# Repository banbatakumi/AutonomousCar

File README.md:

# AutonomousCar

自律走行ミニカー **SURGE Mark.2** の STM32 ファームウェアと基板（回路）。

**技術解説サイト: https://banbatakumi.github.io/surge-mk2/**
ファームの制御（車速制御・TC・ABS・トルクベクタリング・安全層）と基板もこのサイトで解説しています。

> **ファームウェアの最新は [`FW/MainBoard_V3`](https://github.com/banbatakumi/AutonomousCar/tree/FW/MainBoard_V3) ブランチです。**
> 既定ブランチ `main` の `Program/` は古い状態のままです。

## 構成

| ディレクトリ | 内容 |
|---|---|
| `Program/MainF446RE_V3/` | 現行ファーム（STM32F446RE）。最新は上記ブランチ。`Program/MainF446RE`・`MainF446RE_V2` は旧版 |
| `Circuit/` | 基板の設計（`MainBoard_V1`〜`V3_2`、`OtherBoard_V1`） |

## 関連リポジトリ

[`AutonomousCar_RasPi`](https://github.com/banbatakumi/AutonomousCar_RasPi) — Raspberry Pi 側のプログラム。
Pi とは UART（1 Mbps）で通信します。プロトコル（`RAS_PROTOCOL_VERSION`）は Pi 側と**セットで**入れ替えます。

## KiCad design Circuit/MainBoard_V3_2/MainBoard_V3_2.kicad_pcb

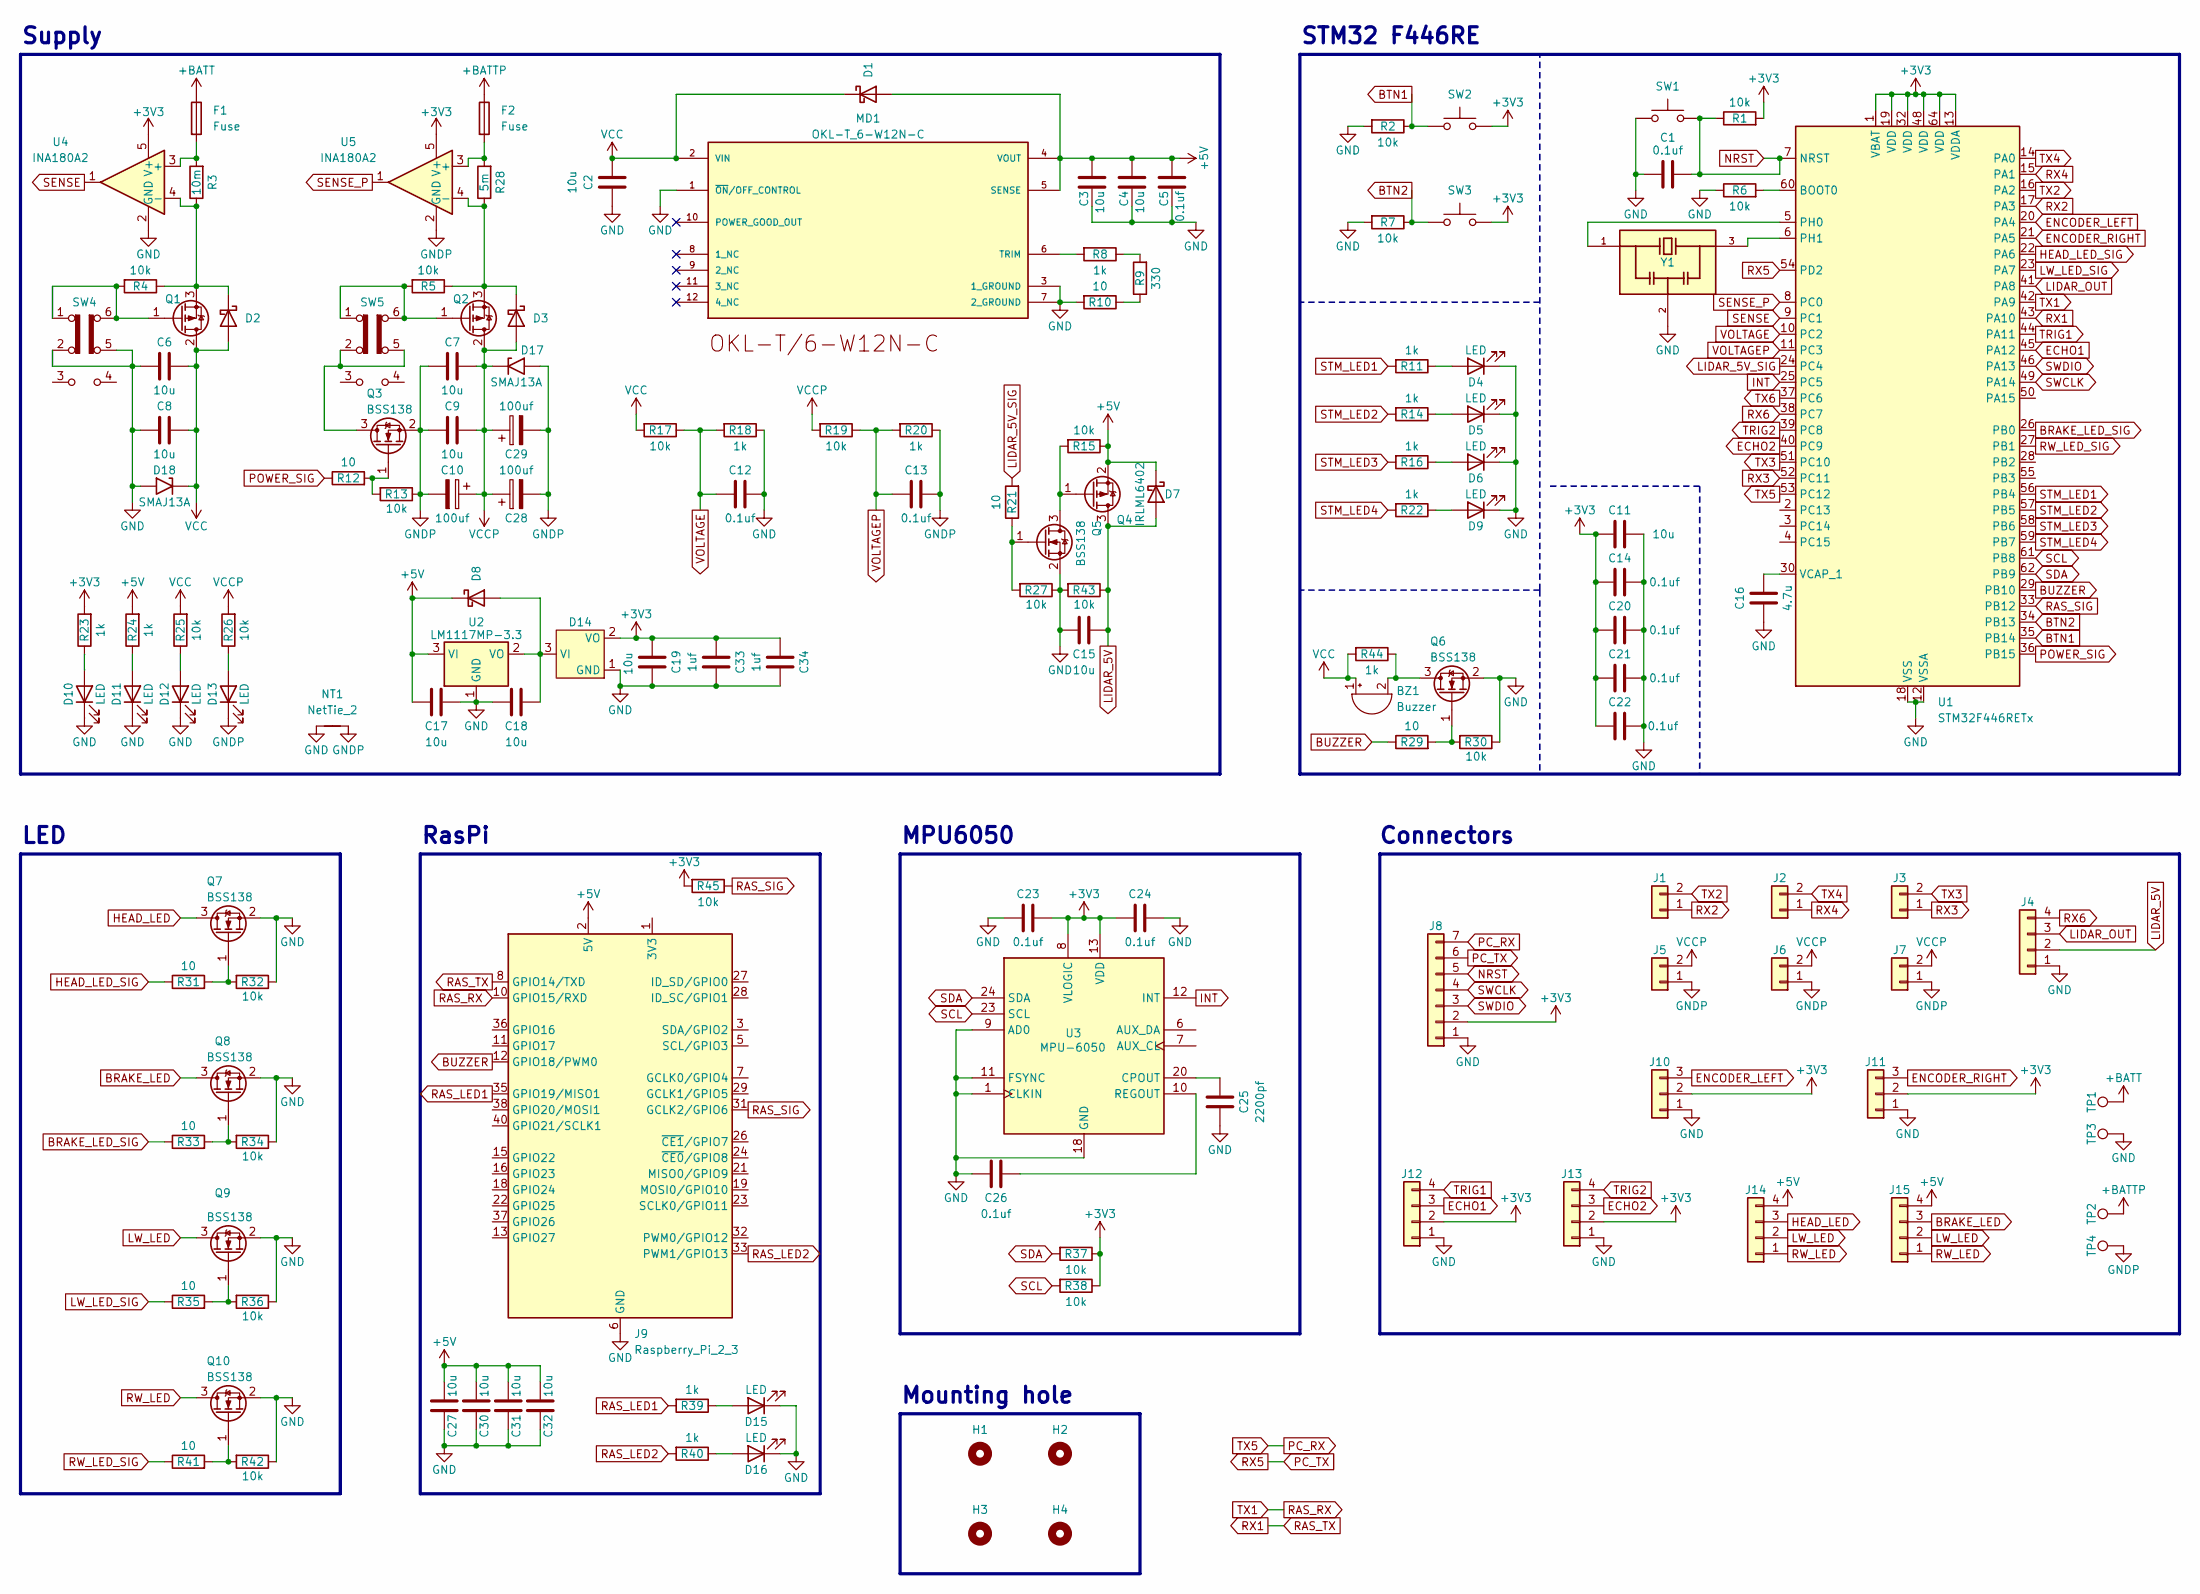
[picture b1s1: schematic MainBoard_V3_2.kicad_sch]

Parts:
BZ1: Buzzer; Buzzer_Murata_PKLCS1212E
C1, C5, C12, C13, C14, C20, C21, C22, C23, C24, C26: 0.1uf; C_0603_1608Metric
C2, C3, C4, C6, C7, C8, C9, C11, C15, C17, C18, C19, C27, C30, C31, C32: 10u; C_0805_2012Metric
C10, C28, C29: 100uf; CP_Radial_D6.3mm_P2.50mm
C16: 4.7u; C_0805_2012Metric
C25: 2200pf; C_0603_1608Metric
C33, C34: 1uf; C_0603_1608Metric
D1, D2, D3, D7, D8: D_Schottky; D_SOD-323_HandSoldering
D4, D5, D6, D9, D10, D11, D12, D13, D15, D16: LED; LED_0603_1608Metric
D14: CH213K; TSOT-23
D17, D18: SMAJ13A; D_SMA
F1, F2: Fuse; Fuseholder_Clip-5x20mm_Keystone_3517_Inline_P23.11x6.76mm_D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
H1, H2, H3, H4: MountingHole; MountingHole_3.2mm_M3_Pad_Via
J1, J2, J3: Conn_01x02; JST_PH_S2B-PH-K_1x02_P2.00mm_Horizontal
J4, J12, J13: Conn_01x04; JST_XH_S4B-XH-A_1x04_P2.50mm_Horizontal
J5, J6, J7: Conn_01x02; Molex_SPOX_5268-02A_1x02_P2.50mm_Horizontal
J8: Conn_01x07; JST_PH_S7B-PH-K_1x07_P2.00mm_Horizontal
J9: Raspberry_Pi_2_3; raspberreyPi
J10, J11: Conn_01x03; JST_PH_S3B-PH-K_1x03_P2.00mm_Horizontal
J14, J15: Conn_01x04; JST_PH_S4B-PH-K_1x04_P2.00mm_Horizontal
MD1: OKL-T_6-W12N-C; MURATA_OKL-T-6-W12N-C_0; MOUSER_PART_NUMBER 580-OKL-T/6-W12N-C; MOUSER_DESCRIPTION Non-Isolated DC/DC Converters 12Vin .59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
NT1: NetTie_2; NetTie-2_SMD_Pad0.5mm
Q1, Q2: Q_PMOS_GDS; TO-252-2
Q3, Q5, Q6, Q7, Q8, Q9, Q10: BSS138; SOT-23
Q4: IRLML6402; SOT-23
R1, R2, R4, R5, R6, R7, R13, R15, R17, R19, R25, R26, R27, R30, R32, R34, R36, R37, R38, R42, R43, R45: 10k; R_0603_1608Metric
R3: 10m; R_1206_3216Metric
R8, R11, R14, R16, R18, R20, R22, R23, R24, R39, R40, R44: 1k; R_0603_1608Metric
R9: 330; R_0603_1608Metric
R10, R12, R21, R29, R31, R33, R35, R41: 10; R_0603_1608Metric
R28: 5m; R_1206_3216Metric
SW1, SW2, SW3: SW_Push; SW_SPST_PTS810
SW4, SW5: SW_Slide_DPDT; IS-2235
TP1, TP2, TP3, TP4: TestPoint; TestPoint_THTPad_D4.0mm_Drill2.0mm
U1: STM32F446RETx; LQFP-64_10x10mm_P0.5mm
U2: LM1117MP-3.3; SOT-223-3_TabPin2
U3: MPU-6050; QFN-24-1EP_4x4mm_P0.5mm_EP2.15x2.15mm
U4, U5: INA180A2; SOT-23-5
Y1: CSTNE16M0V530000R0; Resonator_SMD_Murata_CSTxExxV-3Pin_3.0x1.1mm; PARTREV JGC42-8853B

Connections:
+3V3: C11.1, C14.2, C19.2, C20.2, C21.2, C22.2, C23.1, C24.2, C33.2, C34.2, D14.2 (VO), J8.2, J10.2, J11.2, J12.2, J13.2, R1.2, R23.2, R37.1, R38.1, R45.2, SW2.2, SW3.2, U1.1 (VBAT), U1.13 (VDDA), U1.19 (VDD), U1.32 (VDD), U1.48 (VDD), U1.64 (VDD), U3.8 (VLOGIC), U3.13 (VDD), U4.5 (V+), U5.5 (V+); also elsewhere on the board
+5V: C3.1, C4.1, C5.1, C17.2, C27.1, C30.1, C31.1, C32.1, D1.2 (A), D7.1 (K), D8.1 (K), J9.2 (5V), J9.4 (5V), J14.4, J15.4, MD1.4 (VOUT), MD1.5 (SENSE), Q4.2 (S), R15.1, R24.2, U2.3 (VI); also elsewhere on the board
+BATT: F1.1, TP1.1
+BATTP: F2.1, TP2.1
BRAKE_LED: J15.3, Q8.3 (D)
BRAKE_LED_SIG: R33.1, U1.26 (PB0)
BTN1: R2.1, SW2.1, U1.35 (PB14)
BTN2: R7.1, SW3.1, U1.34 (PB13)
BUZZER: J9.12 (GPIO18/PWM0), R29.1, U1.29 (PB10)
ECHO1: J12.3, U1.45 (PA12)
ECHO2: J13.3, U1.40 (PC9)
ENCODER_LEFT: J10.3, U1.20 (PA4)
ENCODER_RIGHT: J11.3, U1.21 (PA5)
GND: C1.1, C2.1, C3.2, C4.2, C5.2, C6.2, C8.2, C11.2, C12.1, C14.1, C15.2, C16.2, C17.1, C18.2, C19.1, C20.1, C21.1, C22.1, C23.2, C24.1, C25.2, C26.2, C27.2, C30.2, C31.2, C32.2, C33.1, C34.1, D4.1 (K), D5.1 (K), D6.1 (K), D9.1 (K), D10.1 (K), D11.1 (K), D12.1 (K), D14.1 (GND), D15.1 (K), D16.1 (K), D18.2 (A2), J4.1, J8.1, J9.6 (GND), J9.9 (GND), J9.14 (GND), J9.20 (GND), J9.25 (GND), J9.30 (GND), J9.34 (GND), J9.39 (GND), J10.1, J11.1, J12.1, J13.1, MD1.1 (~ON/OFF_CONTROL), MD1.3 (1_GROUND), MD1.7 (2_GROUND), NT1.1, Q5.2 (S), Q6.2 (S), Q7.2 (S), Q8.2 (S), Q9.2 (S), Q10.2 (S), R2.2, R6.1, R7.2, R10.2, R18.1, R27.1, R30.1, R32.1, R34.1, R36.1, R42.1, R43.2, SW1.1, SW4.2 (B), SW4.5 (B), TP3.1, U1.12 (VSSA), U1.18 (VSS), U1.31 (VSS), U1.47 (VSS), U1.63 (VSS), U2.1 (GND), U3.1 (CLKIN), U3.9 (AD0), U3.11 (FSYNC), U3.18 (GND), U4.2 (GND), Y1.2; also elsewhere on the board
GNDP: C7.1, C9.1, C10.2, C13.1, C28.2, C29.2, D13.1 (K), D17.2 (A2), J5.1, J6.1, J7.1, NT1.2, Q3.2 (S), R13.1, R20.1, TP4.1, U5.2 (GND)
HEAD_LED: J14.3, Q7.3 (D)
HEAD_LED_SIG: R31.1, U1.22 (PA6)
INT: U1.25 (PC5), U3.12 (INT)
LIDAR_5V: C15.1, D7.2 (A), J4.2, Q4.3 (D), R43.1
LIDAR_5V_SIG: R21.2, U1.24 (PC4)
LIDAR_OUT: J4.3, U1.41 (PA8)
LW_LED: J14.2, J15.2, Q9.3 (D)
LW_LED_SIG: R35.1, U1.23 (PA7)
NRST: C1.2, J8.5, R1.1, SW1.2, U1.7 (NRST)
unnamed: BZ1.2 (-), Q6.3 (D), R44.1
unnamed: D2.1 (K), Q1.3 (S), R3.1, R4.1, U4.4 (-)
unnamed: D3.1 (K), Q2.3 (S), R5.1, R28.1, U5.4 (-)
unnamed: D4.2 (A), R11.1
unnamed: D5.2 (A), R14.1
unnamed: D6.2 (A), R16.1
unnamed: D9.2 (A), R22.1
unnamed: D10.2 (A), R23.1
unnamed: D11.2 (A), R24.1
unnamed: D12.2 (A), R25.1
unnamed: D13.2 (A), R26.1
unnamed: C18.1, D8.2 (A), D14.3 (VI), U2.2 (VO)
unnamed: D15.2 (A), R39.1
unnamed: D16.2 (A), R40.1
unnamed: J9.1 (3V3), J9.17 (3V3)
unnamed: MD1.6 (TRIM), R8.2
unnamed: Q1.1 (G), R4.2, SW4.1 (A), SW4.6 (C)
unnamed: Q2.1 (G), R5.2, SW5.1 (A), SW5.6 (C)
unnamed: Q3.3 (D), SW5.2 (B), SW5.5 (B)
unnamed: Q3.1 (G), R12.2, R13.2
unnamed: Q4.1 (G), Q5.3 (D), R15.2
unnamed: Q5.1 (G), R21.1, R27.2
unnamed: Q6.1 (G), R29.2, R30.2
unnamed: Q7.1 (G), R31.2, R32.2
unnamed: Q8.1 (G), R33.2, R34.2
unnamed: Q9.1 (G), R35.2, R36.2
unnamed: Q10.1 (G), R41.2, R42.2
unnamed: R8.1, R9.2
unnamed: R9.1, R10.1
unnamed: R6.2, U1.60 (BOOT0)
unnamed: U1.5 (PH0), Y1.1
unnamed: U1.6 (PH1), Y1.3
unnamed: C16.1, U1.30 (VCAP_1)
unnamed: C25.1, U3.20 (CPOUT)
unnamed: C26.1, U3.10 (REGOUT)
unnamed: F1.2, R3.2, U4.3 (+)
unnamed: F2.2, R28.2, U5.3 (+)
PC_RX: J8.7, U1.53 (PC12)
PC_TX: J8.6, U1.54 (PD2)
POWER_SIG: R12.1, U1.36 (PB15)
RAS_LED1: J9.35 (GPIO19/MISO1), R39.2
RAS_LED2: J9.33 (PWM1/GPIO13), R40.2
RAS_RX: J9.10 (GPIO15/RXD), U1.42 (PA9)
RAS_SIG: J9.31 (GCLK2/GPIO6), R45.1, U1.33 (PB12)
RAS_TX: J9.8 (GPIO14/TXD), U1.43 (PA10)
RW_LED: J14.1, J15.1, Q10.3 (D)
RW_LED_SIG: R41.1, U1.27 (PB1)
RX2: J1.1, U1.17 (PA3)
RX3: J3.1, U1.52 (PC11)
RX4: J2.1, U1.15 (PA1)
RX6: J4.4, U1.38 (PC7)
SCL: R38.2, U1.61 (PB8), U3.23 (SCL)
SDA: R37.2, U1.62 (PB9), U3.24 (SDA)
SENSE: U1.9 (PC1), U4.1
SENSE_P: U1.8 (PC0), U5.1
STM_LED1: R11.2, U1.56 (PB4)
STM_LED2: R14.2, U1.57 (PB5)
STM_LED3: R16.2, U1.58 (PB6)
STM_LED4: R22.2, U1.59 (PB7)
SWCLK: J8.4, U1.49 (PA14)
SWDIO: J8.3, U1.46 (PA13)
TRIG1: J12.4, U1.44 (PA11)
TRIG2: J13.4, U1.39 (PC8)
TX2: J1.2, U1.16 (PA2)
TX3: J3.2, U1.51 (PC10)
TX4: J2.2, U1.14 (PA0)
TX6: U1.37 (PC6)
VCC: BZ1.1 (+), C2.2, C6.1, C8.1, D1.1 (K), D2.2 (A), D18.1 (A1), MD1.2 (VIN), Q1.2 (D), R17.2, R25.2, R44.2
VCCP: C7.2, C9.2, C10.1, C28.1, C29.1, D3.2 (A), D17.1 (A1), J5.2, J6.2, J7.2, Q2.2 (D), R19.2, R26.2
VOLTAGE: C12.2, R17.1, R18.2, U1.10 (PC2)
VOLTAGEP: C13.2, R19.1, R20.2, U1.11 (PC3)

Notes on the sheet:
Mounting hole
LED
Supply
MPU6050
RasPi
Connectors
STM32 F446RE

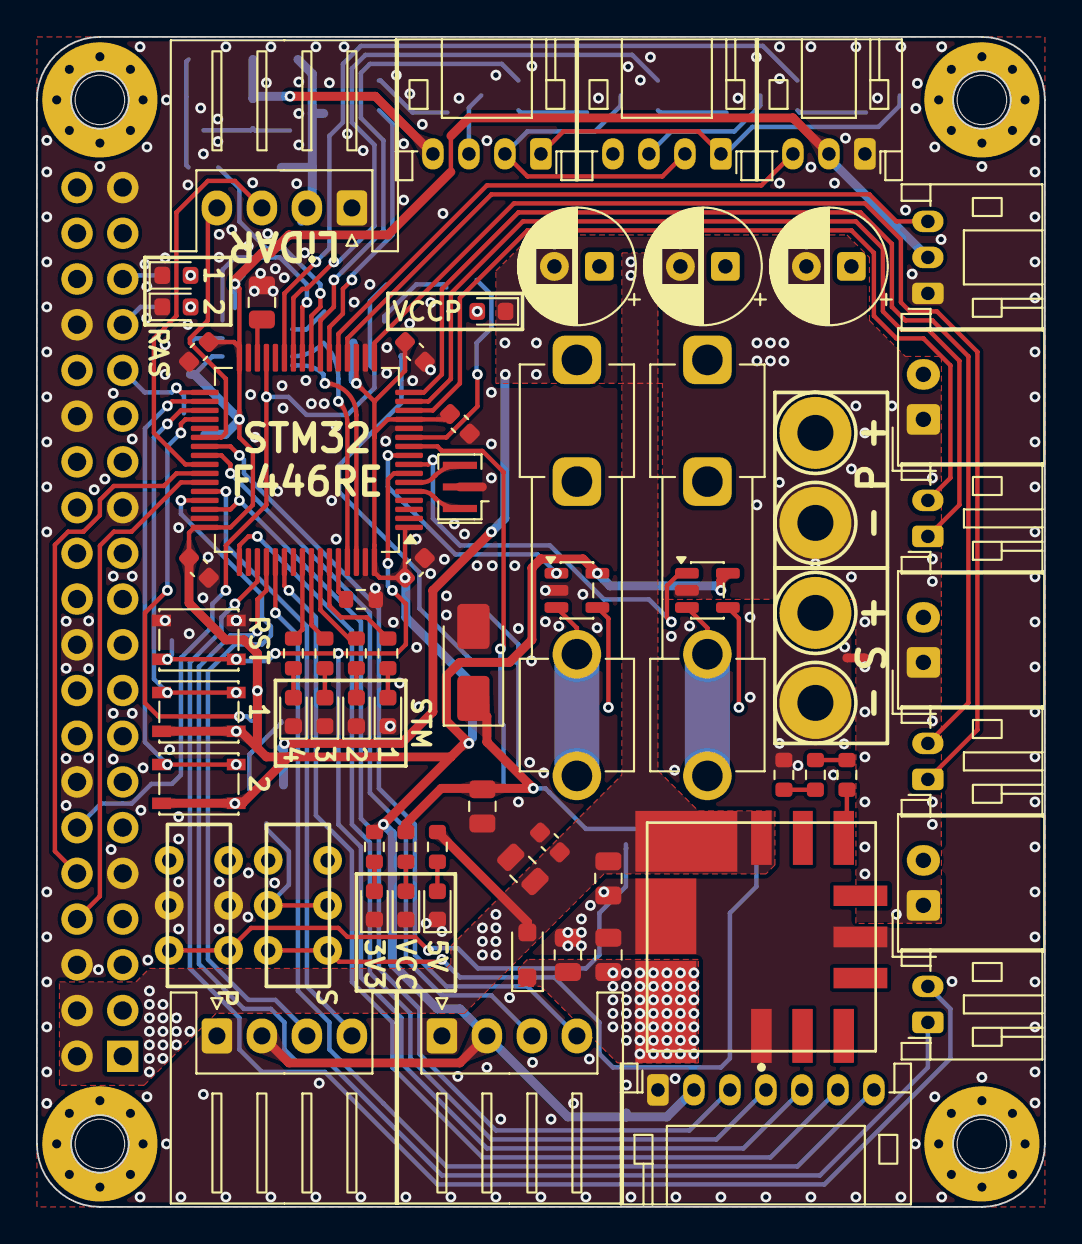
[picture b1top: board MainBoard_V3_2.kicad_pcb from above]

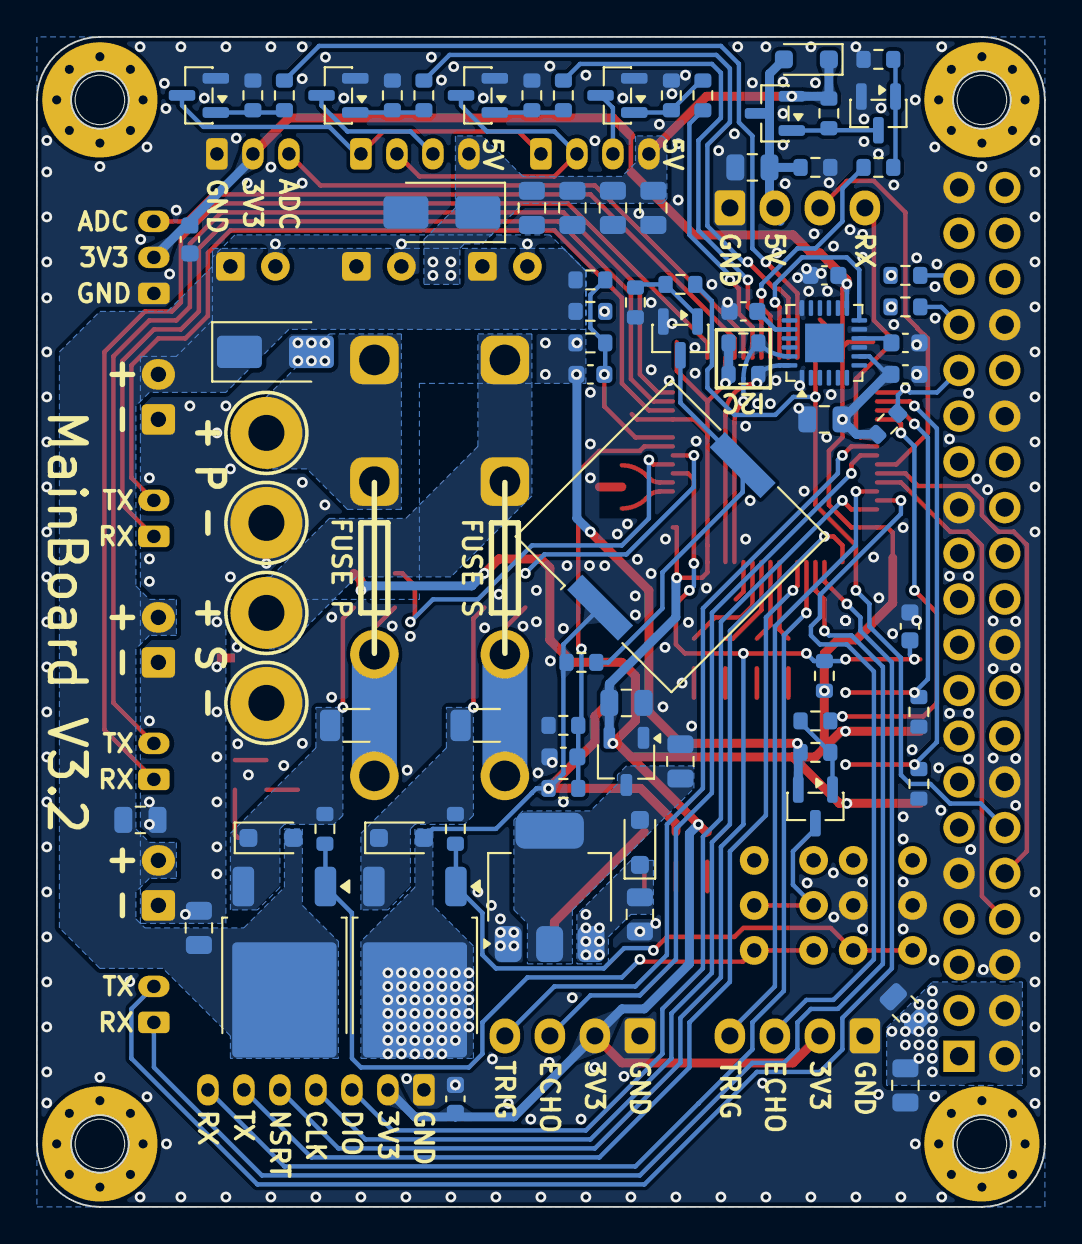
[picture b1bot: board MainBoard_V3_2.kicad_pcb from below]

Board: 2 copper layers, 56.0 x 65.0 mm, 150 parts (80 on the bottom side), 94 nets.

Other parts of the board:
C35: 0.1uf; C_0603_1608Metric
C36, C37: 10u; C_0805_2012Metric
D19: SMAJ5.0A; D_SMA

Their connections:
+3V3: C35.2; also elsewhere on the board
+5V: C36.1, C37.1, D19.1 (A1); also elsewhere on the board
GND: C35.1, C36.2, C37.2, D19.2 (A2); also elsewhere on the board

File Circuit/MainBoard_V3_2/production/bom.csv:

Designator,Footprint,Quantity,Value,LCSC Part #
BZ1,Buzzer_Murata_PKLCS1212E,1,Buzzer,
"C1, C12, C13, C14, C20, C21, C22, C23, C24, C26, C5",0603,11,0.1uf,
"C10, C28, C29",CP_Radial_D6.3mm_P2.50mm,3,100uf,
"C11, C15, C17, C18, C19, C2, C27, C3, C30, C31, C32, C4, C6, C7, C8, C9",0805,16,10u,
C16,0805,1,4.7u,
C25,0603,1,2200pf,
"C33, C34",0603,2,1uf,
"D1, D2, D3, D7, D8",D_SOD-323_HandSoldering,5,D_Schottky,
"D10, D11, D12, D13, D15, D16, D4, D5, D6, D9",0603,10,LED,
D14,TSOT-23,1,CH213K,
"D17, D18",D_SMA,2,SMAJ13A,
"F1, F2",Fuseholder_Clip-5x20mm_Keystone_3517_Inline_P23.11x6.76mm_D1.70mm_Horizontal,2,Fuse,
"J1, J2, J3",JST_PH_S2B-PH-K_1x02_P2.00mm_Horizontal,3,Conn_01x02,
"J10, J11",JST_PH_S3B-PH-K_1x03_P2.00mm_Horizontal,2,Conn_01x03,
"J12, J13, J4",JST_XH_S4B-XH-A_1x04_P2.50mm_Horizontal,3,Conn_01x04,
"J14, J15",JST_PH_S4B-PH-K_1x04_P2.00mm_Horizontal,2,Conn_01x04,
"J5, J6, J7",Molex_SPOX_5268-02A_1x02_P2.50mm_Horizontal,3,Conn_01x02,
J8,JST_PH_S7B-PH-K_1x07_P2.00mm_Horizontal,1,Conn_01x07,
J9,raspberreyPi,1,Raspberry_Pi_2_3,
MD1,MURATA_OKL-T-6-W12N-C_0,1,OKL-T_6-W12N-C,OKL-T/6-W12N-C
"Q1, Q2",TO-252-2,2,Q_PMOS_GDS,
"Q10, Q3, Q5, Q6, Q7, Q8, Q9",SOT-23,7,BSS138,
Q4,SOT-23,1,IRLML6402,
"R1, R13, R15, R17, R19, R2, R25, R26, R27, R30, R32, R34, R36, R37, R38, R4, R42, R43, R45, R5, R6, R7",0603,22,10k,
"R10, R12, R21, R29, R31, R33, R35, R41",0603,8,10,
"R11, R14, R16, R18, R20, R22, R23, R24, R39, R40, R44, R8",0603,12,1k,
R28,1206,1,5m,
R3,1206,1,10m,
R9,0603,1,330,
"SW1, SW2, SW3",SW_SPST_PTS810,3,SW_Push,
"SW4, SW5",IS-2235,2,SW_Slide_DPDT,
"TP1, TP2, TP3, TP4",TestPoint_THTPad_D4.0mm_Drill2.0mm,4,TestPoint,
U1,LQFP-64_10x10mm_P0.5mm,1,STM32F446RETx,
U2,SOT-223-3_TabPin2,1,LM1117MP-3.3,
U3,QFN-24-1EP_4x4mm_P0.5mm_EP2.15x2.15mm,1,MPU-6050,
"U4, U5",SOT-23-5,2,INA180A2,
Y1,Resonator_SMD_Murata_CSTxExxV-3Pin_3.0x1.1mm,1,CSTNE16M0V530000R0,

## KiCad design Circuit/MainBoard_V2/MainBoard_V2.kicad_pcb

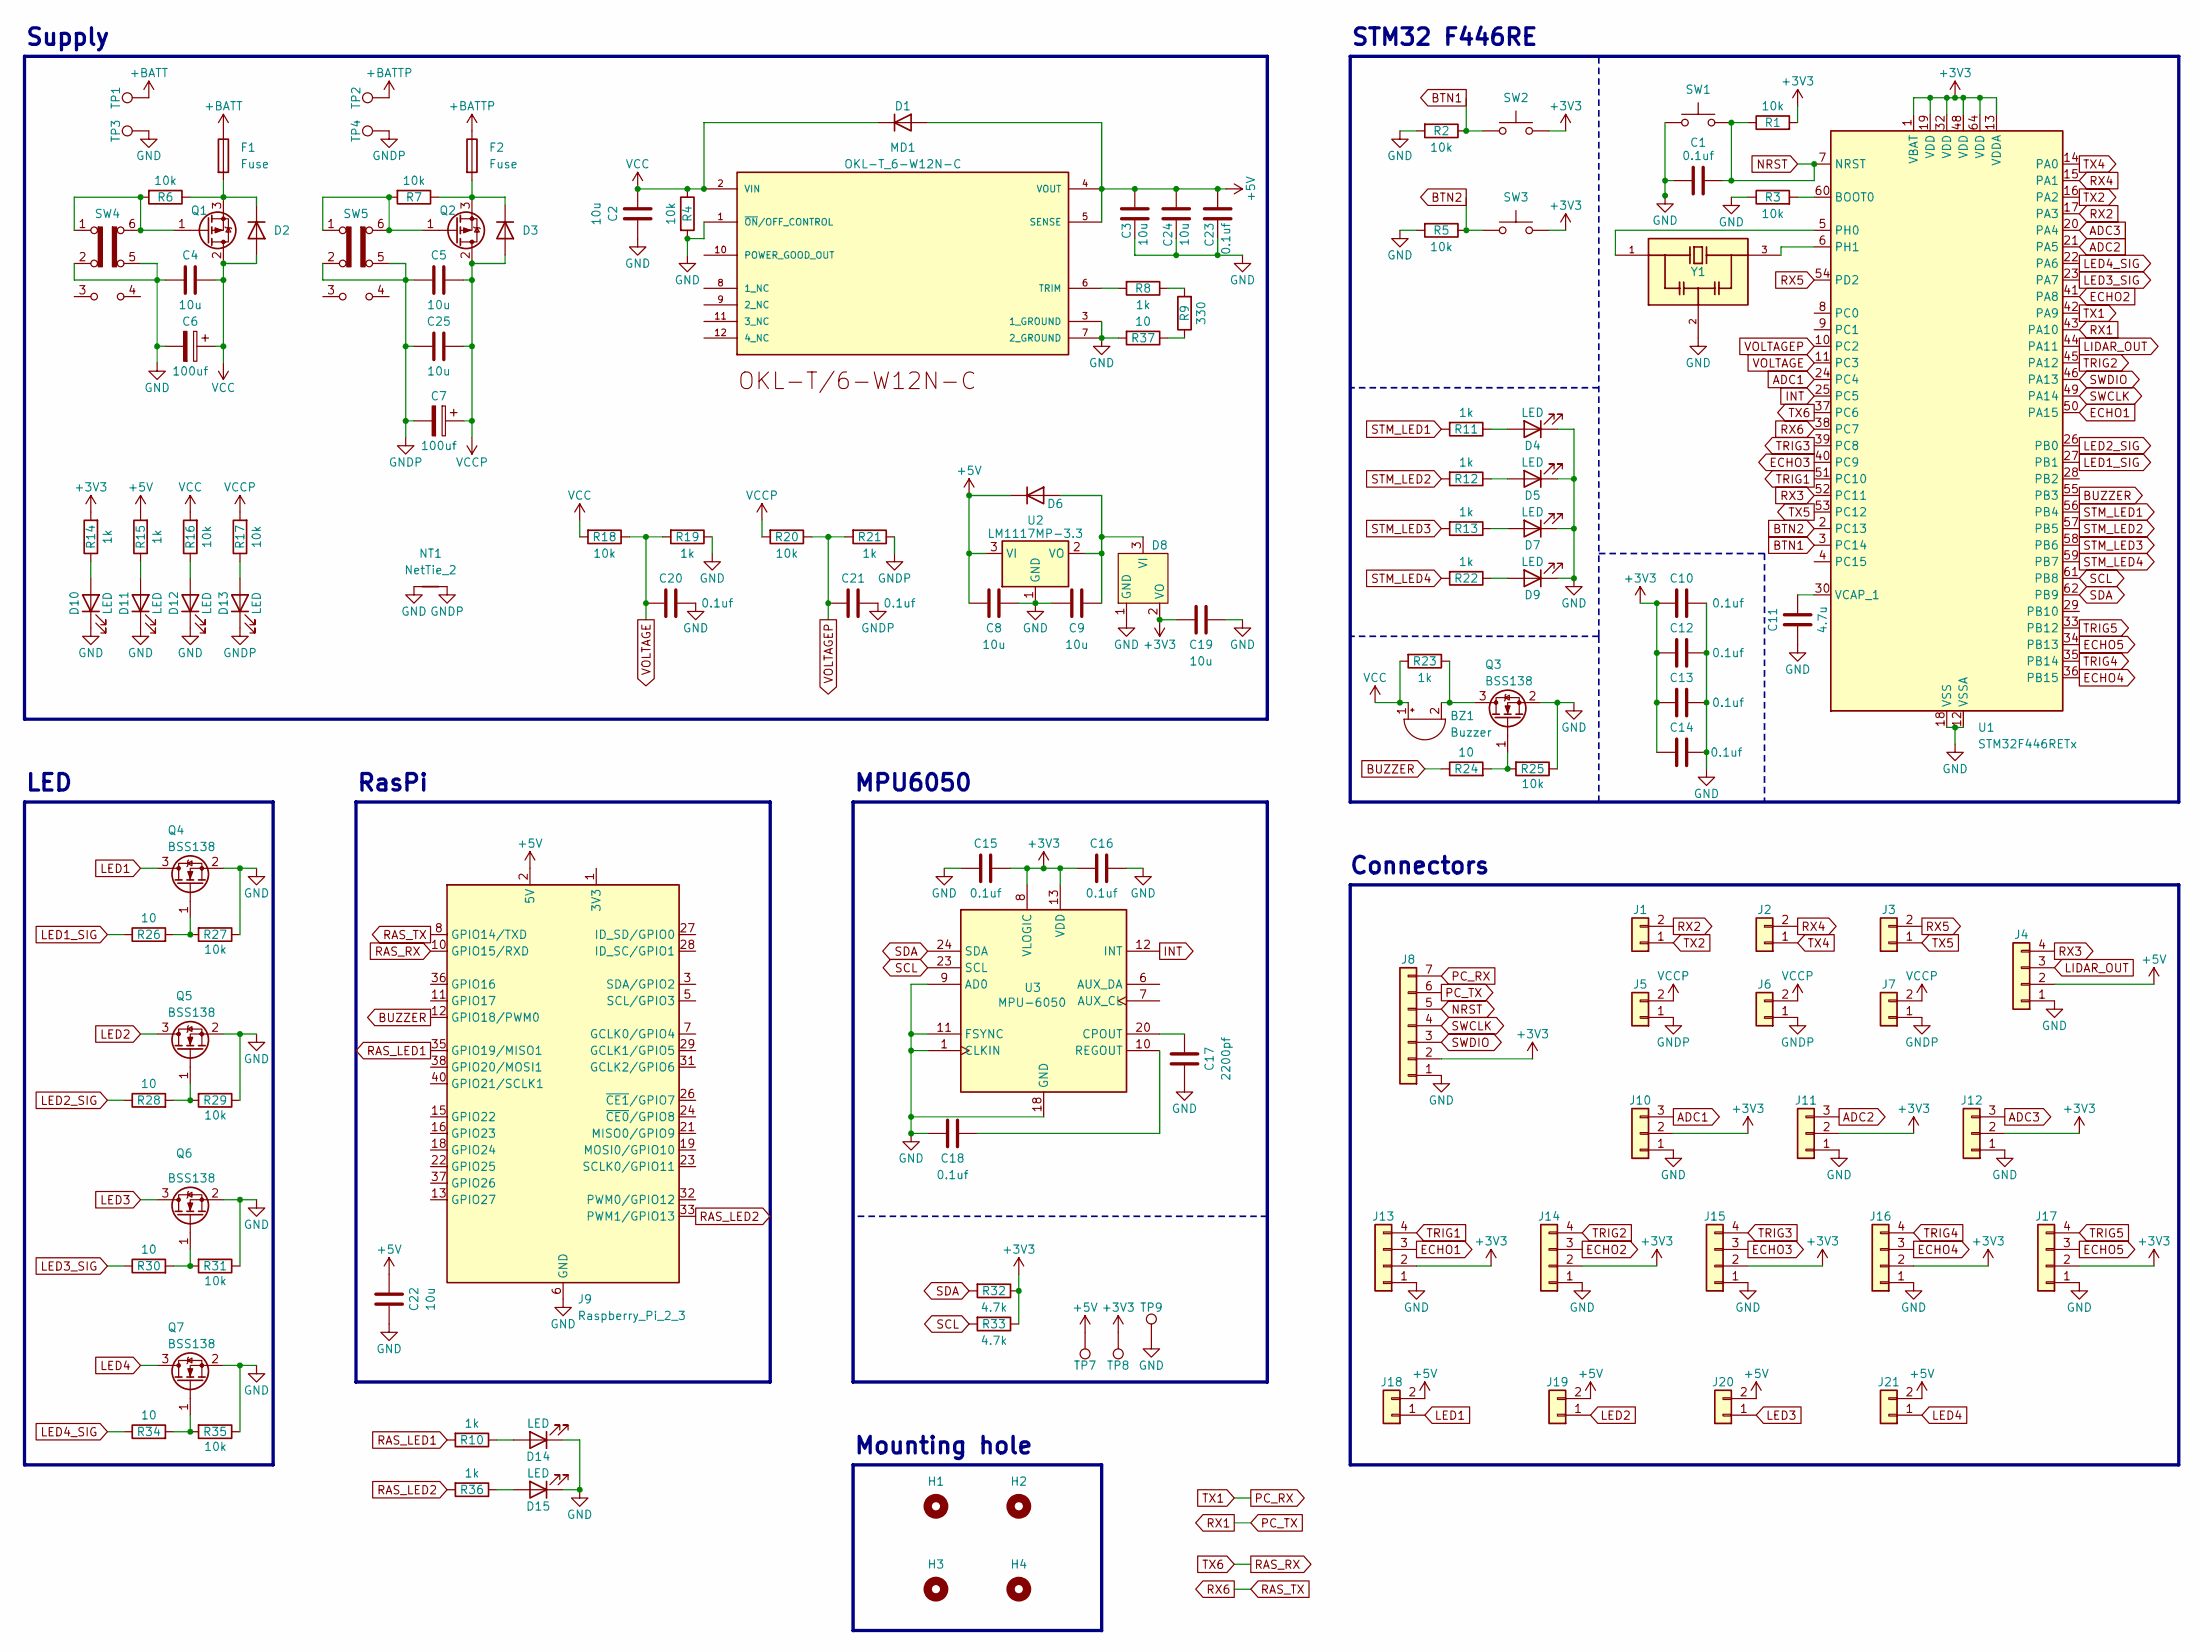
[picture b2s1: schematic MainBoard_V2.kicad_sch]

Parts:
BZ1: Buzzer; Buzzer_Murata_PKLCS1212E
C1, C10, C12, C13, C14, C15, C16, C18, C20, C21, C23: 0.1uf; C_0603_1608Metric
C2, C3, C4, C5, C8, C9, C19, C22, C24, C25: 10u; C_0805_2012Metric
C6, C7: 100uf; CP_Radial_D6.3mm_P2.50mm
C11: 4.7u; C_0805_2012Metric
C17: 2200pf; C_0603_1608Metric
D1, D2, D3, D6: 1N4148W; D_SOD-123
D4, D5, D7, D9, D10, D11, D12, D13, D14, D15: LED; LED_0603_1608Metric
D8: CH213K; TSOT-23
F1, F2: Fuse; Fuseholder_Clip-5x20mm_Keystone_3517_Inline_P23.11x6.76mm_D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
H1, H2, H3, H4: MountingHole; MountingHole_3.2mm_M3_Pad_Via
J1, J2, J3: Conn_01x02; JST_PH_B2B-PH-K_1x02_P2.00mm_Vertical
J4, J13, J14, J15, J16, J17: Conn_01x04; JST_XH_B4B-XH-A_1x04_P2.50mm_Vertical
J5, J6, J7, J18, J19, J20, J21: Conn_01x02; JST_XH_B2B-XH-A_1x02_P2.50mm_Vertical
J8: Conn_01x07; JST_PH_B7B-PH-K_1x07_P2.00mm_Vertical
J9: Raspberry_Pi_2_3; raspberreyPi_2_3
J10, J11, J12: Conn_01x03; JST_XH_B3B-XH-A_1x03_P2.50mm_Vertical
MD1: OKL-T_6-W12N-C; MURATA_OKL-T-6-W12N-C_0; MOUSER_PART_NUMBER 580-OKL-T/6-W12N-C; MOUSER_DESCRIPTION Non-Isolated DC/DC Converters 12Vin .59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
NT1: NetTie_2; NetTie-2_SMD_Pad0.5mm
Q1, Q2: Q_PMOS_GDS; TO-252-2
Q3, Q4, Q5, Q6, Q7: BSS138; SOT-23
R1, R2, R3, R4, R5, R6, R7, R16, R17, R18, R20, R25, R27, R29, R31, R35: 10k; R_0603_1608Metric
R8, R10, R11, R12, R13, R14, R15, R19, R21, R22, R23, R36: 1k; R_0603_1608Metric
R9: 330; R_0603_1608Metric
R24, R26, R28, R30, R34, R37: 10; R_0603_1608Metric
R32, R33: 4.7k; R_0603_1608Metric
SW1, SW2, SW3: SW_Push; SW_SPST_PTS810
SW4, SW5: SW_Slide_DPDT; IS-2235
TP1, TP2, TP3, TP4: TestPoint; TestPoint_THTPad_D4.0mm_Drill2.0mm
TP7, TP8, TP9: TestPoint; TestPoint_THTPad_D1.0mm_Drill0.5mm
U1: STM32F446RETx; LQFP-64_10x10mm_P0.5mm
U2: LM1117MP-3.3; SOT-223-3_TabPin2
U3: MPU-6050; InvenSense_QFN-24_4x4mm_P0.5mm
Y1: CSTNE16M0V530000R0; Resonator_SMD_Murata_CSTxExxV-3Pin_3.0x1.1mm; PARTREV JGC42-8853B

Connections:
+3V3: C10.2, C12.2, C13.2, C14.2, C15.1, C16.2, C19.2, D8.2 (VO), J8.2, J10.2, J11.2, J12.2, J13.2, J14.2, J15.2, J16.2, J17.2, R1.2, R14.2, R32.1, R33.1, SW2.2, SW3.2, TP8.1, U1.1 (VBAT), U1.13 (VDDA), U1.19 (VDD), U1.32 (VDD), U1.48 (VDD), U1.64 (VDD), U3.8 (VLOGIC), U3.13 (VDD); also elsewhere on the board
+5V: C3.1, C8.2, C22.1, C23.1, C24.1, D1.2 (A), D6.1 (K), J4.2, J9.2 (5V), J9.4 (5V), J18.2, J19.2, J20.2, J21.2, MD1.4 (VOUT), MD1.5 (SENSE), R15.2, TP7.1, U2.3 (VI)
+BATT: F1.1, TP1.1
+BATTP: F2.1, TP2.1
ADC1: J10.3, U1.24 (PC4)
ADC2: J11.3, U1.21 (PA5)
ADC3: J12.3, U1.20 (PA4)
BTN1: R2.1, SW2.1, U1.3 (PC14)
BTN2: R5.1, SW3.1, U1.2 (PC13)
BUZZER: J9.12 (GPIO18/PWM0), R24.1, U1.55 (PB3)
ECHO1: J13.3, U1.50 (PA15)
ECHO2: J14.3, U1.41 (PA8)
ECHO3: J15.3, U1.40 (PC9)
ECHO4: J16.3, U1.36 (PB15)
ECHO5: J17.3, U1.34 (PB13)
GND: C1.1, C2.1, C3.2, C4.2, C6.2, C8.1, C9.2, C10.1, C11.2, C12.1, C13.1, C14.1, C15.2, C16.1, C17.2, C18.2, C19.1, C20.1, C22.2, C23.2, C24.2, D4.1 (K), D5.1 (K), D7.1 (K), D8.1 (GND), D9.1 (K), D10.1 (K), D11.1 (K), D12.1 (K), D14.1 (K), D15.1 (K), J4.1, J8.1, J9.6 (GND), J9.9 (GND), J9.14 (GND), J9.20 (GND), J9.25 (GND), J9.30 (GND), J9.34 (GND), J9.39 (GND), J10.1, J11.1, J12.1, J13.1, J14.1, J15.1, J16.1, J17.1, MD1.1 (~ON/OFF_CONTROL), MD1.3 (1_GROUND), MD1.7 (2_GROUND), NT1.1, Q3.2 (S), Q4.2 (S), Q5.2 (S), Q6.2 (S), Q7.2 (S), R2.2, R3.1, R4.2, R5.2, R19.1, R25.1, R27.1, R29.1, R31.1, R35.1, R37.2, SW1.1, SW4.2 (B), SW4.5 (B), TP3.1, TP9.1, U1.12 (VSSA), U1.18 (VSS), U1.31 (VSS), U1.47 (VSS), U1.63 (VSS), U2.1 (GND), U3.1 (CLKIN), U3.9 (AD0), U3.11 (FSYNC), U3.18 (GND), Y1.2; also elsewhere on the board
GNDP: C5.1, C7.2, C21.1, C25.1, D13.1 (K), J5.1, J6.1, J7.1, NT1.2, R21.1, SW5.2 (B), SW5.5 (B), TP4.1
INT: U1.25 (PC5), U3.12 (INT)
LED1: J18.1, Q4.3 (D)
LED1_SIG: R26.1, U1.27 (PB1)
LED2: J19.1, Q5.3 (D)
LED2_SIG: R28.1, U1.26 (PB0)
LED3: J20.1, Q6.3 (D)
LED3_SIG: R30.1, U1.23 (PA7)
LED4: J21.1, Q7.3 (D)
LED4_SIG: R34.1, U1.22 (PA6)
LIDAR_OUT: J4.3, U1.44 (PA11)
NRST: C1.2, J8.5, R1.1, SW1.2, U1.7 (NRST)
unnamed: BZ1.2 (-), Q3.3 (D), R23.1
unnamed: D2.1 (K), F1.2, Q1.3 (S), R6.1
unnamed: D3.1 (K), F2.2, Q2.3 (S), R7.1
unnamed: D4.2 (A), R11.1
unnamed: D5.2 (A), R12.1
unnamed: C9.1, D6.2 (A), D8.3 (VI), U2.2 (VO)
unnamed: D7.2 (A), R13.1
unnamed: D9.2 (A), R22.1
unnamed: D10.2 (A), R14.1
unnamed: D11.2 (A), R15.1
unnamed: D12.2 (A), R16.1
unnamed: D13.2 (A), R17.1
unnamed: D14.2 (A), R10.1
unnamed: D15.2 (A), R36.1
unnamed: J9.1 (3V3), J9.17 (3V3)
unnamed: MD1.6 (TRIM), R8.2
unnamed: Q1.1 (G), R6.2, SW4.1 (A), SW4.6 (C)
unnamed: Q2.1 (G), R7.2, SW5.1 (A), SW5.6 (C)
unnamed: Q3.1 (G), R24.2, R25.2
unnamed: Q4.1 (G), R26.2, R27.2
unnamed: Q5.1 (G), R28.2, R29.2
unnamed: Q6.1 (G), R30.2, R31.2
unnamed: Q7.1 (G), R34.2, R35.2
unnamed: R8.1, R9.2
unnamed: R9.1, R37.1
unnamed: R3.2, U1.60 (BOOT0)
unnamed: U1.5 (PH0), Y1.1
unnamed: U1.6 (PH1), Y1.3
unnamed: C11.1, U1.30 (VCAP_1)
unnamed: C17.1, U3.20 (CPOUT)
unnamed: C18.1, U3.10 (REGOUT)
PC_RX: J8.7, U1.42 (PA9)
PC_TX: J8.6, U1.43 (PA10)
RAS_LED1: J9.35 (GPIO19/MISO1), R10.2
RAS_LED2: J9.33 (PWM1/GPIO13), R36.2
RAS_RX: J9.10 (GPIO15/RXD), U1.37 (PC6)
RAS_TX: J9.8 (GPIO14/TXD), U1.38 (PC7)
RX2: J1.2, U1.17 (PA3)
RX3: J4.4, U1.52 (PC11)
RX4: J2.2, U1.15 (PA1)
RX5: J3.2, U1.54 (PD2)
SCL: R33.2, U1.61 (PB8), U3.23 (SCL)
SDA: R32.2, U1.62 (PB9), U3.24 (SDA)
STM_LED1: R11.2, U1.56 (PB4)
STM_LED2: R12.2, U1.57 (PB5)
STM_LED3: R13.2, U1.58 (PB6)
STM_LED4: R22.2, U1.59 (PB7)
SWCLK: J8.4, U1.49 (PA14)
SWDIO: J8.3, U1.46 (PA13)
TRIG1: J13.4, U1.51 (PC10)
TRIG2: J14.4, U1.45 (PA12)
TRIG3: J15.4, U1.39 (PC8)
TRIG4: J16.4, U1.35 (PB14)
TRIG5: J17.4, U1.33 (PB12)
TX2: J1.1, U1.16 (PA2)
TX4: J2.1, U1.14 (PA0)
TX5: J3.1, U1.53 (PC12)
VCC: BZ1.1 (+), C2.2, C4.1, C6.1, D1.1 (K), D2.2 (A), MD1.2 (VIN), Q1.2 (D), R4.1, R16.2, R18.2, R23.2
VCCP: C5.2, C7.1, C25.2, D3.2 (A), J5.2, J6.2, J7.2, Q2.2 (D), R17.2, R20.2
VOLTAGE: C20.2, R18.1, R19.2, U1.11 (PC3)
VOLTAGEP: C21.2, R20.1, R21.2, U1.10 (PC2)

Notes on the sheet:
Mounting hole
MPU6050
Connectors
Supply
STM32 F446RE
LED
RasPi

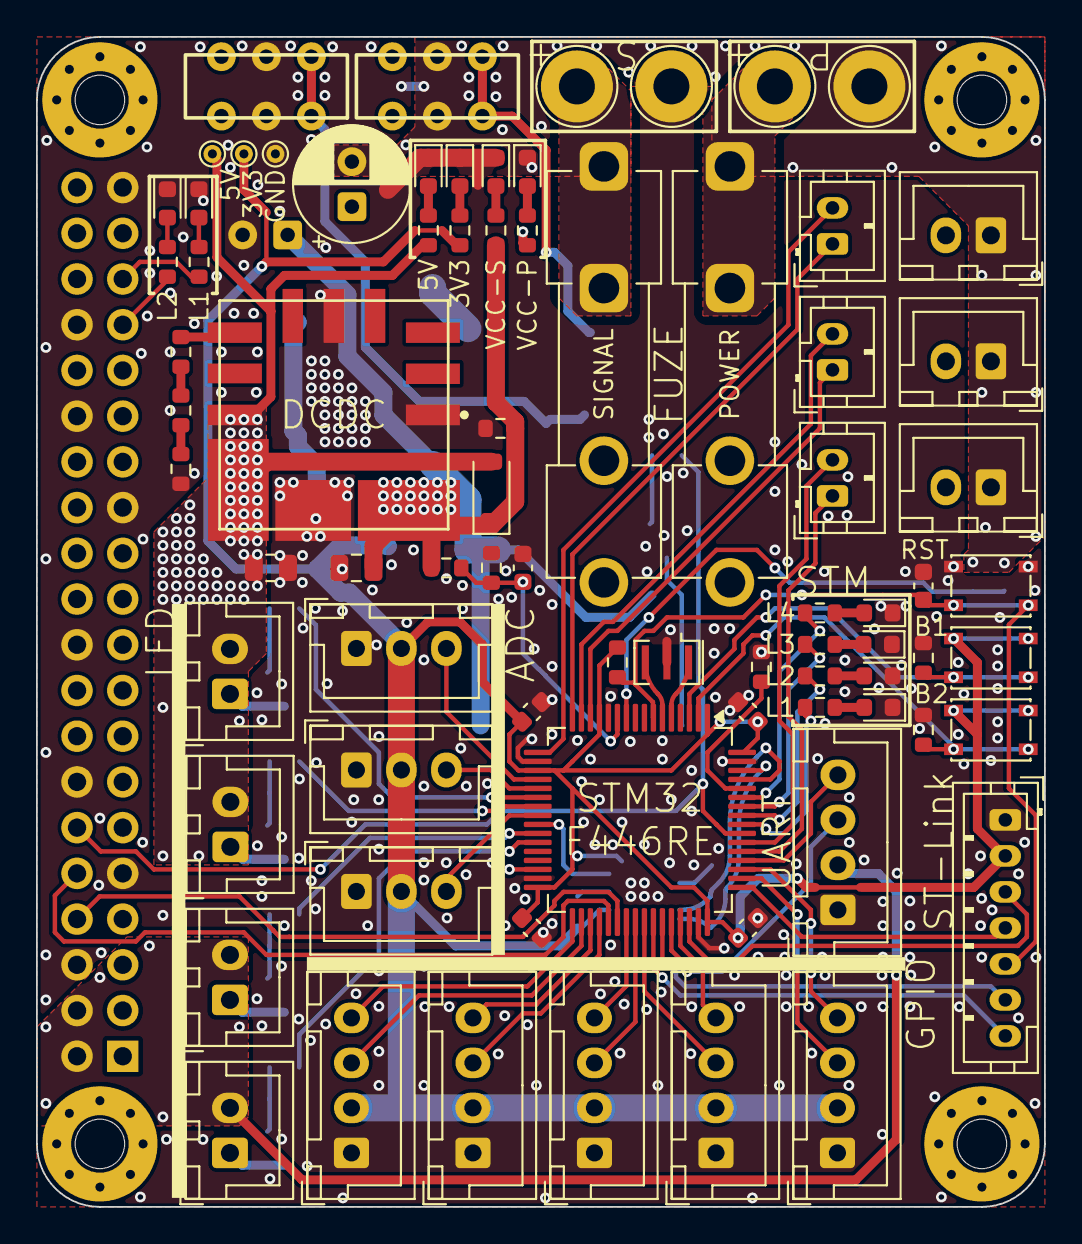
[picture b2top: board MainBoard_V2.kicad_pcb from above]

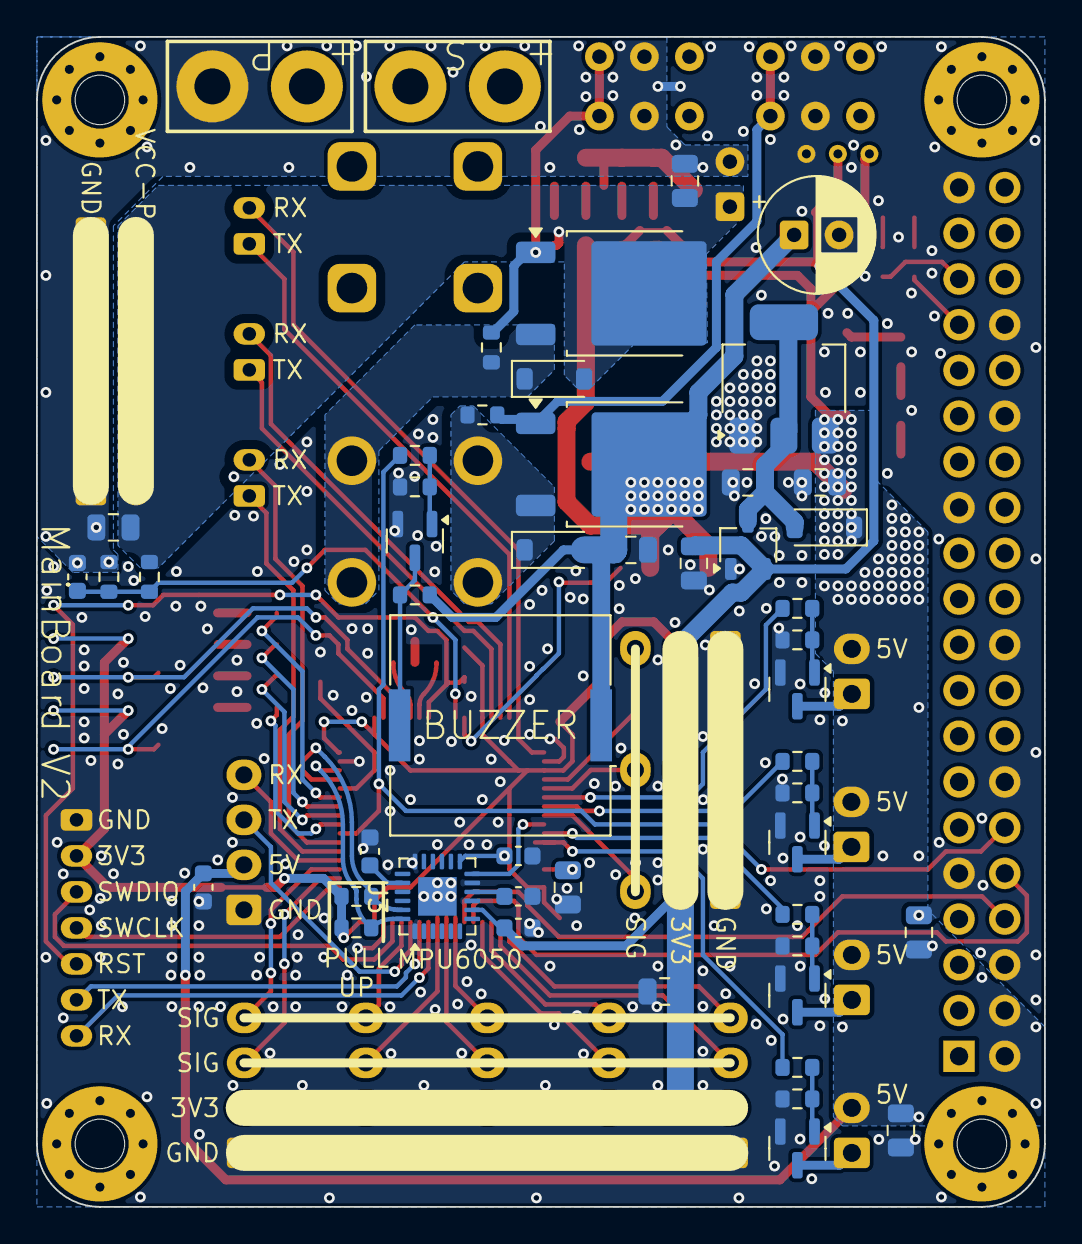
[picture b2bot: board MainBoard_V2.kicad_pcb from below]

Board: 2 copper layers, 56.0 x 65.0 mm, 131 parts (49 on the bottom side), 89 nets.

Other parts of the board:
C26: 10u; C_0805_2012Metric

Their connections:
+3V3: C26.1; also elsewhere on the board
GND: C26.2; also elsewhere on the board

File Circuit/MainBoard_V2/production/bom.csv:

Designator,Footprint,Quantity,Value,LCSC Part #
BZ1,Buzzer_Murata_PKLCS1212E,1,Buzzer,
"C1, C10, C12, C13, C14, C15, C16, C18, C20, C21",0603,10,0.1uf,
C11,0805,1,4.7u,
C17,0603,1,2200pf,
"C19, C2, C3, C4, C5, C8, C9",0805,7,10u,
"C6, C7",CP_Radial_D6.3mm_P2.50mm,2,100uf,
"D1, D2, D3, D6",D_SOD-123,4,1N4148W,
"D10, D11, D12, D13, D14, D15, D4, D5, D7, D9",0603,10,LED,
D8,TSOT-23,1,CH213K,
"F1, F2",Fuseholder_Clip-5x20mm_Keystone_3517_Inline_P23.11x6.76mm_D1.70mm_Horizontal,2,Fuse,
"J1, J2, J3",JST_PH_B2B-PH-K_1x02_P2.00mm_Vertical,3,Conn_01x02,
"J10, J11, J12",JST_XH_B3B-XH-A_1x03_P2.50mm_Vertical,3,Conn_01x03,
"J13, J14, J15, J16, J17, J4",JST_XH_B4B-XH-A_1x04_P2.50mm_Vertical,6,Conn_01x04,
"J18, J19, J20, J21, J5, J6, J7",JST_XH_B2B-XH-A_1x02_P2.50mm_Vertical,7,Conn_01x02,
J8,JST_PH_B7B-PH-K_1x07_P2.00mm_Vertical,1,Conn_01x07,
J9,raspberreyPi_2_3,1,Raspberry_Pi_2_3,
MD1,MURATA_OKL-T-6-W12N-C_0,1,OKL-T_6-W12N-C,OKL-T/6-W12N-C
"Q1, Q2",TO-252-2,2,Q_PMOS_GDS,
"Q3, Q4, Q5, Q6, Q7",SOT-23,5,BSS138,
"R1, R16, R17, R18, R2, R20, R25, R27, R29, R3, R31, R35, R4, R5, R6, R7",0603,16,10k,
"R10, R11, R12, R13, R14, R15, R19, R21, R22, R23, R36, R8",0603,12,1k,
"R24, R26, R28, R30, R34, R37",0603,6,10,
"R32, R33",0603,2,4.7k,
R9,0603,1,330,
"SW1, SW2, SW3",SW_SPST_PTS810,3,SW_Push,
"SW4, SW5",IS-2235,2,SW_Slide_DPDT,
"TP1, TP2, TP3, TP4",TestPoint_THTPad_D4.0mm_Drill2.0mm,4,TestPoint,
"TP7, TP8, TP9",TestPoint_THTPad_D1.0mm_Drill0.5mm,3,TestPoint,
U1,LQFP-64_10x10mm_P0.5mm,1,STM32F446RETx,
U2,SOT-223-3_TabPin2,1,LM1117MP-3.3,
U3,InvenSense_QFN-24_4x4mm_P0.5mm,1,MPU-6050,
Y1,Resonator_SMD_Murata_CSTxExxV-3Pin_3.0x1.1mm,1,CSTNE16M0V530000R0,
